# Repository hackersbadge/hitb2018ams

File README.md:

# Hacker's Badge for Hack In The Box 2018, Amsterdam

- [x] Hardware: WhiteA10n3
- [x] Code: KLKS + xwings (partial)

* MCU: STM32F103
* Flash: W25Q32
* 1.3 inch OLED
* 433Mhz RF Receiver
* IR Receiver
* 6 Buttons (Up, Down, Left, Right, OK, ESC)
* 6 x RGB LED

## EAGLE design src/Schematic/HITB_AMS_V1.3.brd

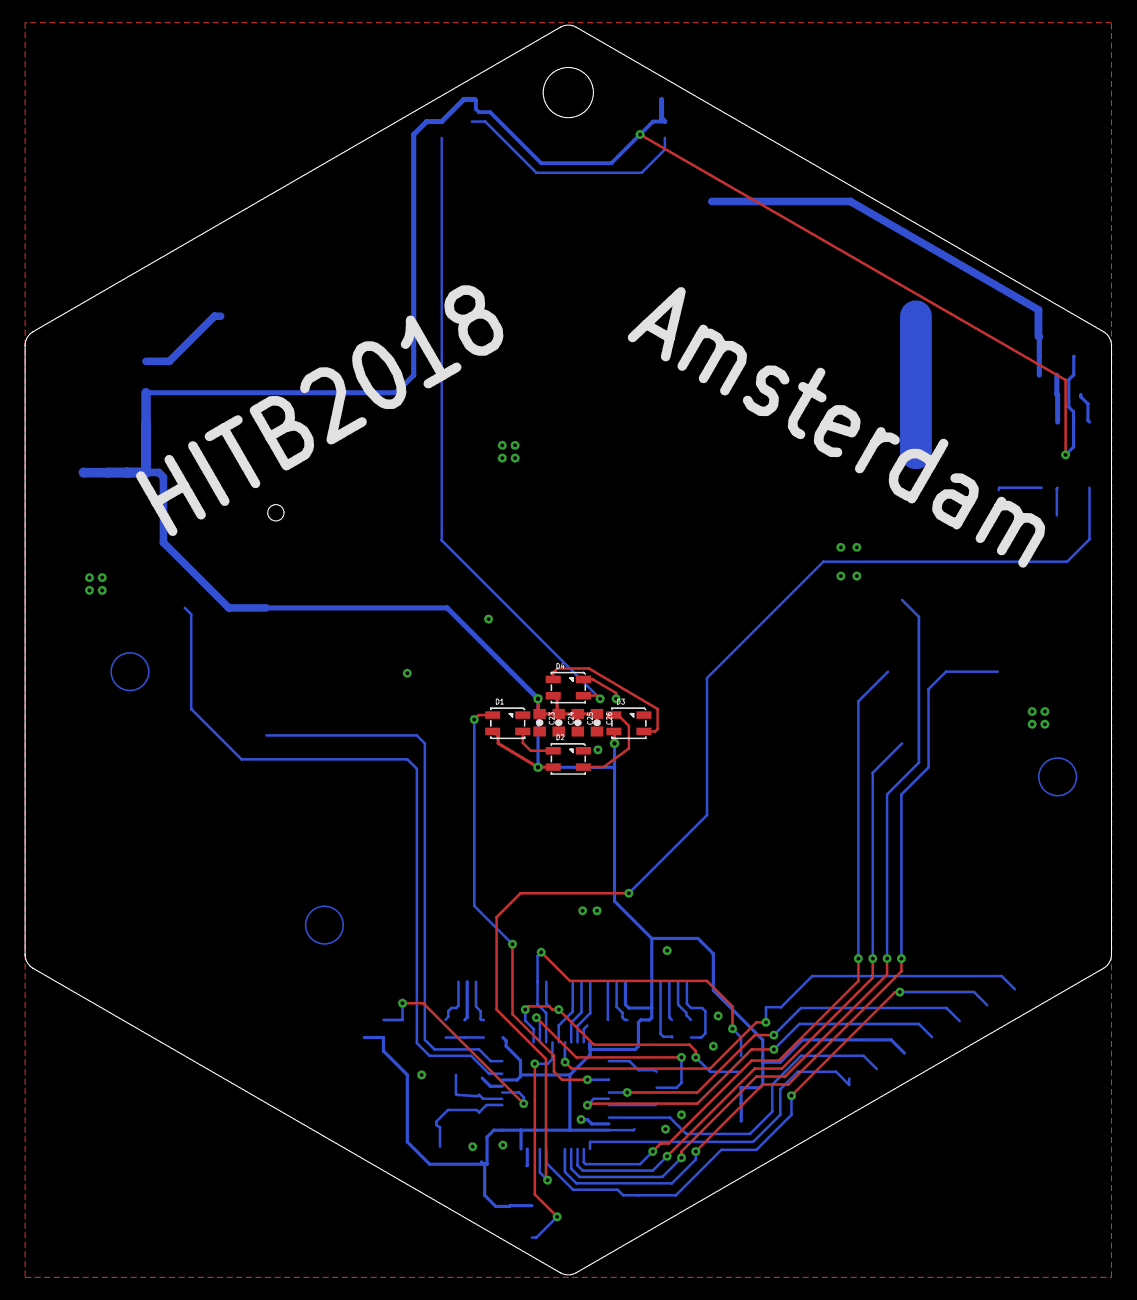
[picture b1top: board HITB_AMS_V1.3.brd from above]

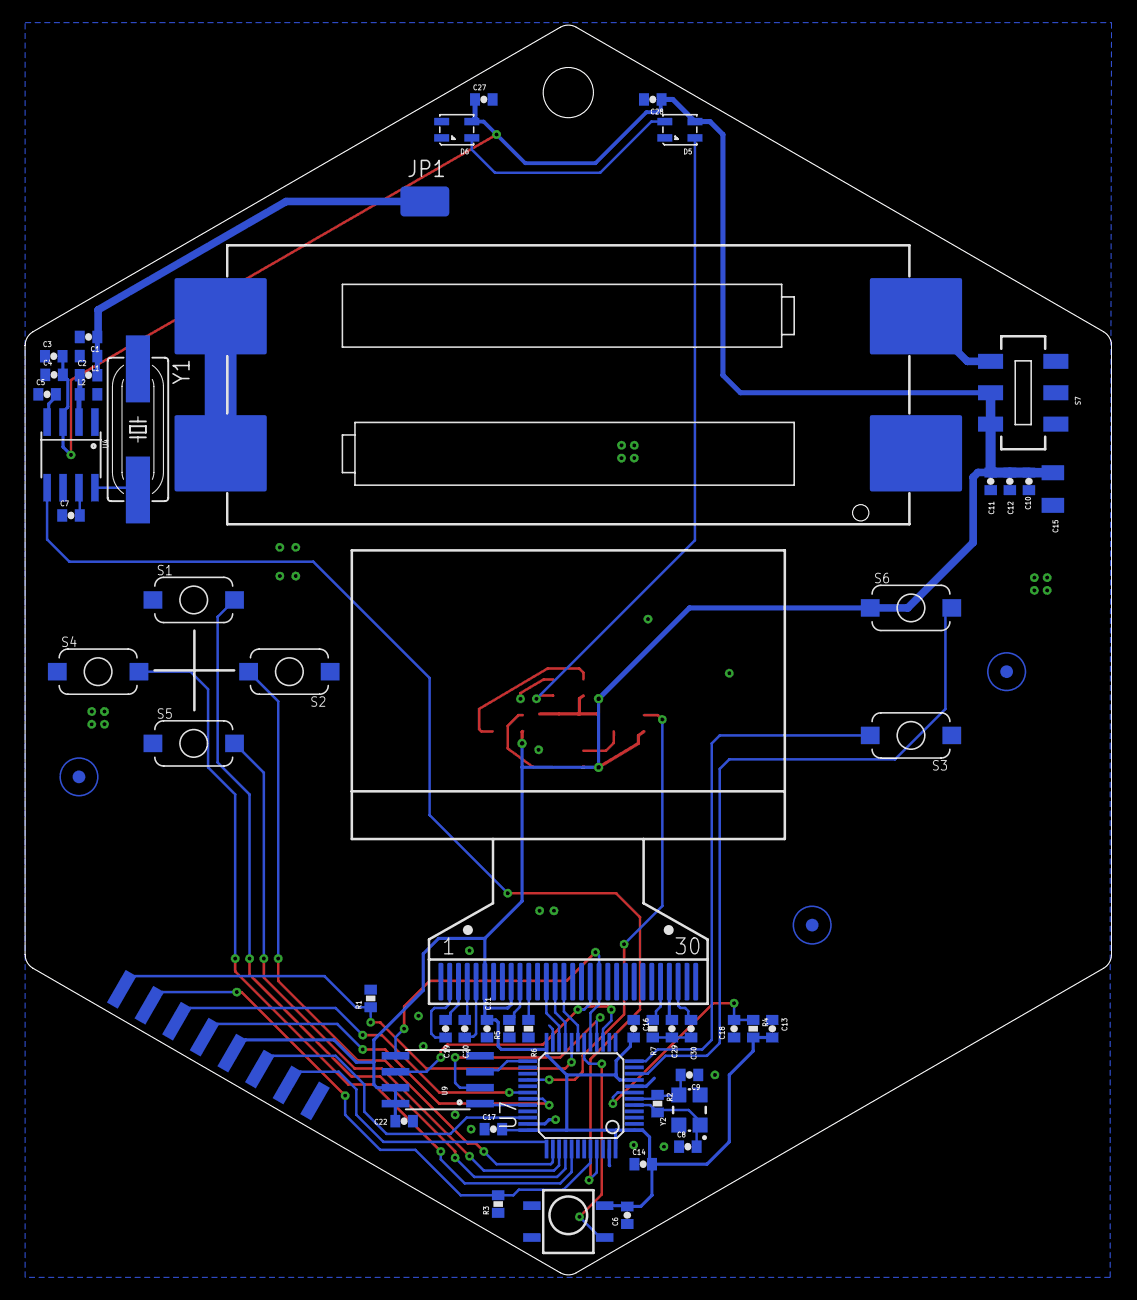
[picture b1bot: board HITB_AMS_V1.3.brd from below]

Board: 2 copper layers, 86.6 x 99.6 mm, 67 parts (59 on the bottom side), 49 nets.

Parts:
C1: 5.6pF NP0; 0603-CAP
C2: 1.5pF; 0603-CAP
C3: 100pF; 0603-CAP
C4, C6, C13, C14, C16, C17, C18, C23, C24, C25, C26, C27, C28: 0.1uF; 0603-CAP
C5: 0.47uF; 0603-CAP
C7, C10, C21, C22: 1uF; 0603-CAP
C8, C9: 22pF; 0603-CAP
C11: 10uF; 0603-CAP
C12: 22uF; 0603-CAP
C15: 47uF; 1206
C19, C20: 1uF 16V X5R; 0603-CAP
C29: 4.7uF 16V X7R; 0603-CAP
C30: 2.2uF; 0603-CAP
D1, D2, D3, D4, D5, D6: XT1511-2427; RGB_2427
JP1: M01SMD; LUXEON-PAD
JP2, JP3: 1X04_TEST_2
L1: 22nH; 0603
L2: 27nH; 0603
R1, R3, R4: 10k; 0603-RES
R2: 10M; 0603-RES
R5, R6: 4k7; 0603-RES
R7: 910K; 0603-RES
S1, S2, S3, S4, S5, S6: SWITCH_2_T; BUTTON_TSSURX
S7: SWITCH-DPDT; MSS22D18
U1, U2, U3: FIDUCIALMOUNT; FIDUCIA-MOUNT
U4: SYN480R; SO08
U5: IRM-H638T/TR2; IR_RECEIVE
U6: 360UNICORN_LOGO_0.8_STOP; 360UNICORN_S0.8
U7: STM32F103C8T6; TQFP48
U8: BATTER_AAA_2_3; BATTER_AAA_3
U9: W25Q32; SO08-EIAJ
U10: OLED_12864_1.3
Y1: 6.7458MHz; HC49UP
Y2: 8MHz; CRYSTAL-SMD-3225

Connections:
3.3V: C3.2, C4.2, C6.2, C10.2, C11.2, C12.2, C13.2, C14.2, C15.1, C16.2, C17.2, C21.1, C22.1, C23.1, C24.1, C25.1, C26.1, C27.1, C28.1, D1.4, D2.4, D3.4, D4.4, D5.4, D6.4, JP3.4, R4.2, S6.P$1, S7.1, S7.2, U4.3, U5.4, U7.1, U7.9, U7.24, U7.36, U7.48, U9.7, U9.8, U10.6, U10.9
ANT: C1.1, C2.2, JP1.P$1, L1.1
GND: C1.2, C3.1, C4.1, C5.1, C6.1, C7.1, C8.1, C9.1, C10.1, C11.1, C12.1, C13.1, C14.1, C15.2, C16.1, C17.1, C18.1, C21.2, C22.2, C23.2, C24.2, C25.2, C26.2, C27.2, C28.2, C29.2, C30.2, D1.2, D2.2, D3.2, D4.2, D5.2, D6.2, JP3.1, L1.2, L2.2, R1.2, R3.1, R5.1, R6.1, R7.1, S1.P$1, S2.P$1, S3.P$1, S4.P$1, S5.P$1, S7.4, S7.5, S7.6, U4.1, U4.6, U5.1, U5.2, U7.8, U7.23, U7.35, U7.47, U8.A-, U9.4, U10.1, U10.8, U10.12, U10.16, U10.17, U10.21, U10.22, U10.23, U10.24, U10.25, U10.29, U10.30, Y1.1
IR: U5.3, U7.18
KEY_DOWN: S5.P$2, U7.39
KEY_ESC: S3.P$2, U7.12
KEY_LEFT: S4.P$2, U7.41
KEY_OK: S6.P$2, U7.10
KEY_RIGHT: S2.P$2, U7.38
KEY_UP: S1.P$2, U7.40
LCD_A0: U7.19, U10.15
LCD_CS: U7.22, U10.13
LCD_RES: U7.21, U10.14
MISO: U7.16, U9.2
MOSI: U7.17, U9.5, U10.19
MOSI2: D1.3, U7.28
unnamed: D3.1, D4.3
unnamed: C8.2, R2.2, U7.5, Y2.1
unnamed: R5.2, U10.10
unnamed: C9.2, R2.1, U7.6, Y2.3
unnamed: U8.A+, U8.B-
unnamed: D4.1, D5.3
unnamed: D5.1, D6.3
unnamed: S7.3, U8.B+
unnamed: C29.1, U10.27
unnamed: C19.2, U10.2
unnamed: C19.1, U10.3
unnamed: C20.1, U10.4
unnamed: C20.2, U10.5
unnamed: C30.1, U10.28
unnamed: R7.2, U10.26
unnamed: R6.2, U10.11
unnamed: C2.1, L2.1, U4.2
unnamed: C5.2, U4.4
unnamed: C7.2, U4.7
unnamed: U4.8, Y1.2
unnamed: D2.1, D3.3
unnamed: D1.1, D2.3
RF: U4.5, U7.45
SCK: U7.15, U9.6, U10.18
STM32_BOOT0: JP2.3, R3.2, U7.44
STM32_BOOT1: JP2.4, R1.1, U7.20
STM32_RST: C18.2, R4.1, U7.7
STM32_RX: JP2.1, U7.31
STM32_TX: JP2.2, U7.30
SWCLK: JP3.2, U7.37
SWDIO: JP3.3, U7.34
W25Q_CS: U7.32, U9.1
W25Q_WP: U7.25, U9.3

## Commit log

2018-11-22 initial commit for amsterdam
2018-11-22 added black readme
2018-11-22 added source
2018-11-22 more desc and pics
2018-11-22 test image

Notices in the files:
parts and their libraries:
2SparkFun: Licensing: CC v3.0 Share-Alike You are welcome to use this library for commercial purposes.
